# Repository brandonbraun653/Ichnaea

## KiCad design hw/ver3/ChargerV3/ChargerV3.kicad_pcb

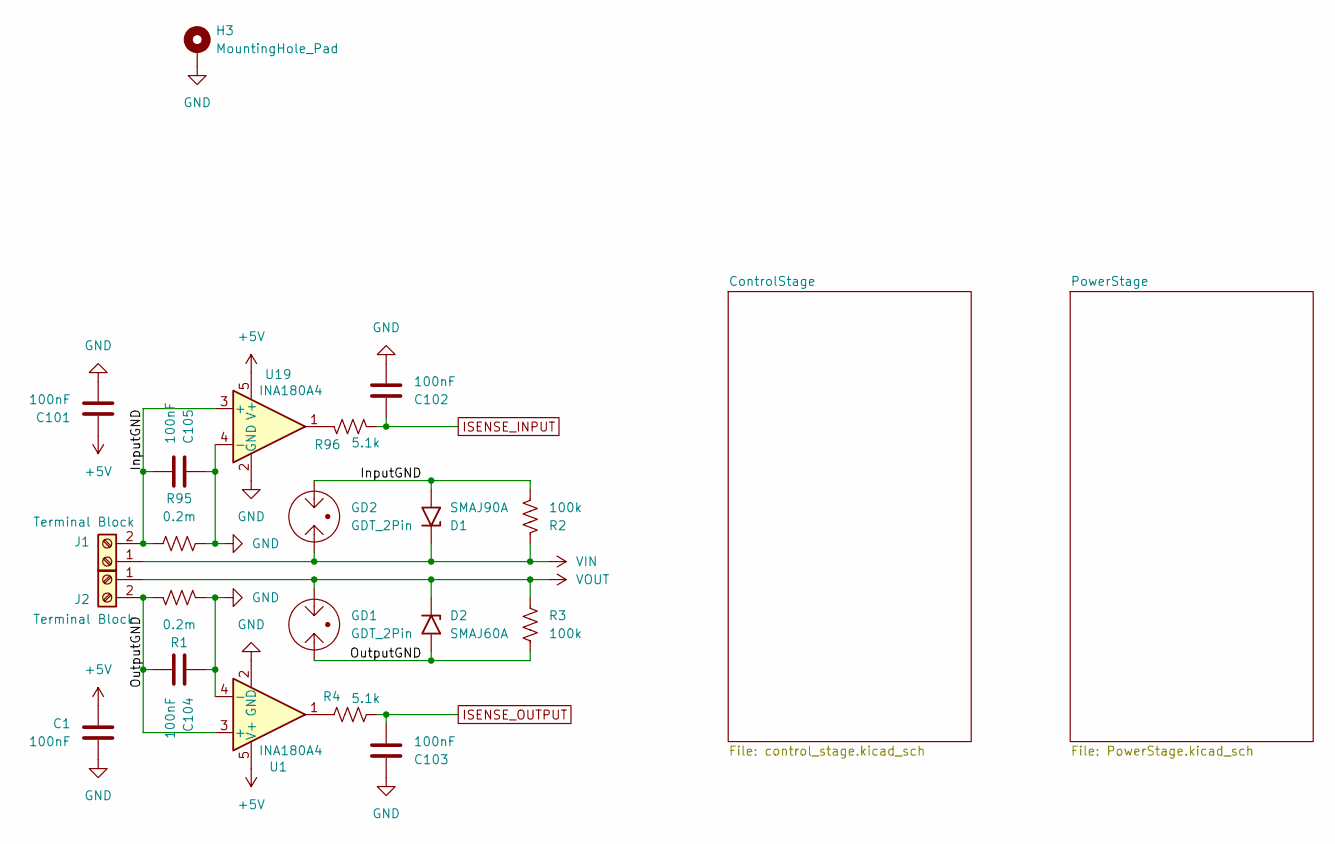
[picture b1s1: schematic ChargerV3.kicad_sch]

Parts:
C1, C101, C102, C103, C104, C105: 100nF; C_0603_1608Metric; LCSC C14663
D1: SMAJ90A; D_SMA; LCSC C2989723
D2: SMAJ60A; D_SMA; LCSC C707480
GD1, GD2: GDT_2Pin; Fuse_1812_4532Metric_Pad1.30x3.40mm_HandSolder; LCSC C78323
H3: MountingHole_Pad; MountingHole_3.2mm_M3_Pad_Via; Digikey N/A
J1, J2: Terminal Block; KF88SA-16.0-2P; LCSC C707749
R1, R95: 0.2m; Shunt_5930; LCSC C22446543
R2, R3: 100k; R_1206_3216Metric; LCSC C17900
R4, R96: 5.1k; R_0603_1608Metric; LCSC C23186
U1, U19: INA180A4; SOT-23-5; LCSC C188337

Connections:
+5V: C1.1, C101.1, U1.5 (V+), U19.5 (V+); also elsewhere on the board
/InputGND: C105.2, D1.2 (A2), GD2.2, J1.2, R2.2, R95.1, U19.3 (+)
/OutputGND: C104.2, D2.2 (A2), GD1.1, J2.2, R1.1, R3.2, U1.3 (+)
GND: C1.2, C101.2, C102.2, C103.1, C104.1, C105.1, H3.1, R1.2, R95.2, U1.2 (GND), U1.4 (-), U19.2 (GND), U19.4 (-); also elsewhere on the board
ISENSE_INPUT: C102.1, R96.1; also elsewhere on the board
ISENSE_OUTPUT: C103.2, R4.1; also elsewhere on the board
unnamed: R4.2, U1.1
unnamed: R96.2, U19.1
VIN: D1.1 (A1), GD2.1, J1.1, R2.1; also elsewhere on the board
VOUT: D2.1 (A1), GD1.2, J2.1, R3.1; also elsewhere on the board

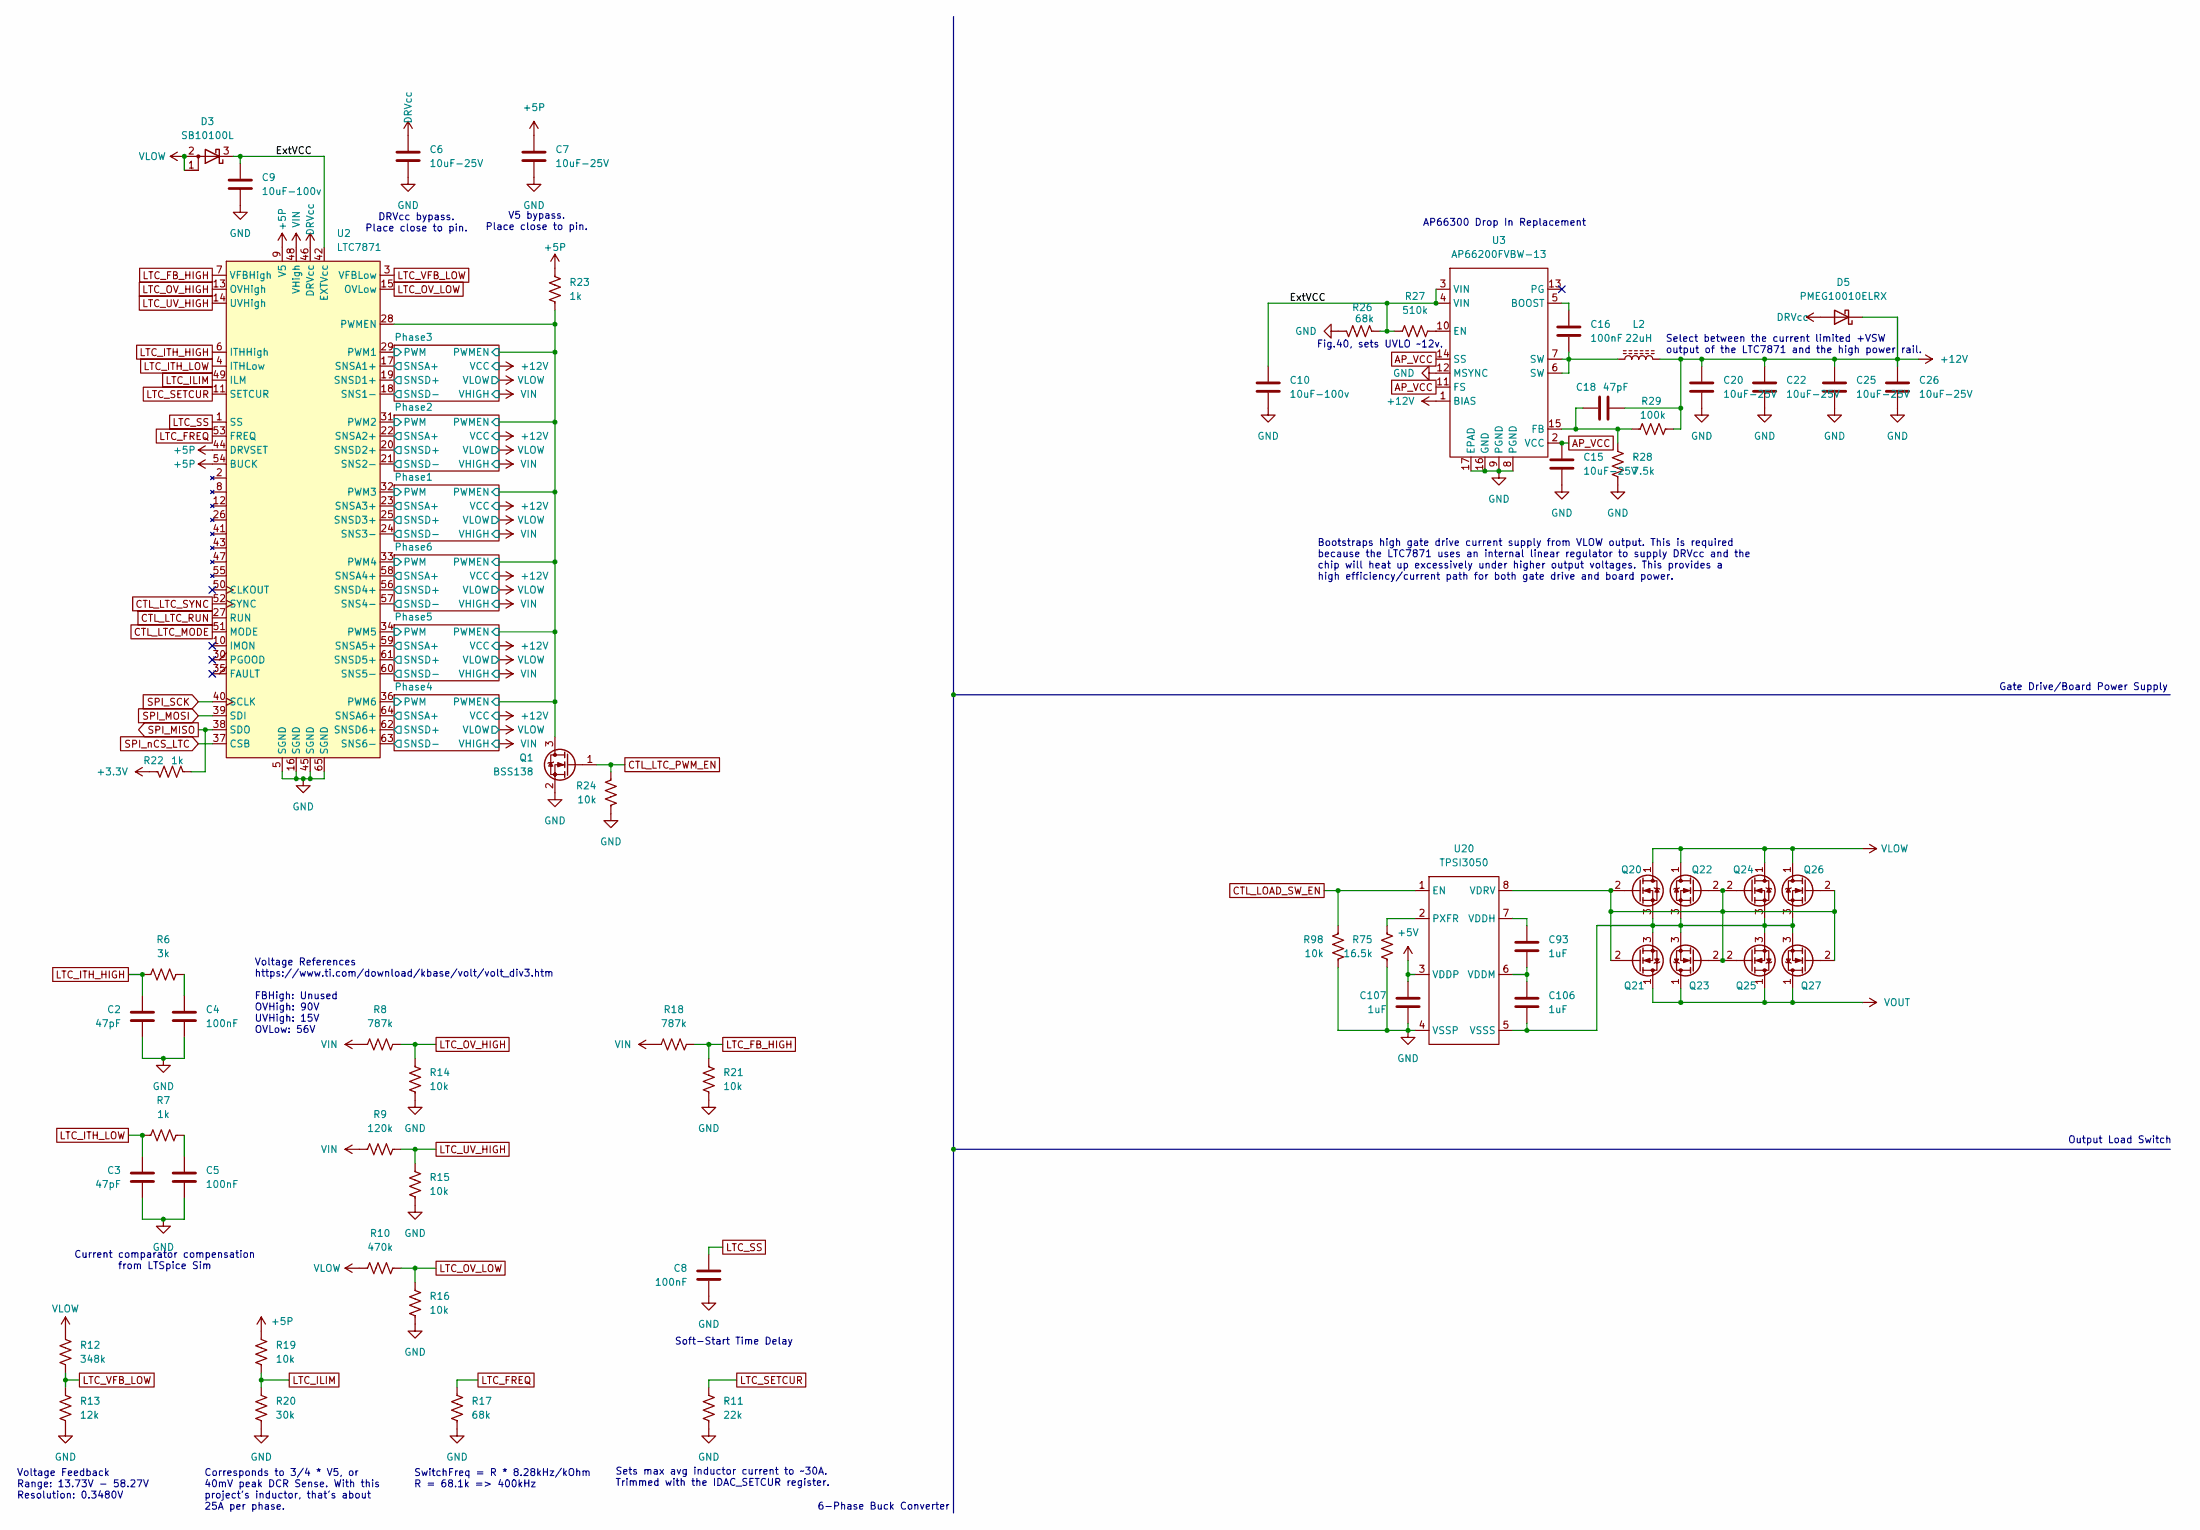
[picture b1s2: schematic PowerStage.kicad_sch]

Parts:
C2, C3, C18: 47pF; C_0603_1608Metric; LCSC C1671
C4, C5, C8, C16: 100nF; C_0603_1608Metric; LCSC C14663
C6: 10uF-25V; C_0603_1608Metric; Voltage 25; Digikey N/A
C7, C15, C20, C22, C25, C26: 10uF-25V; C_0603_1608Metric; Digikey N/A
C9, C10: 10uF-100v; C_1210_3225Metric_Pad1.33x2.70mm_HandSolder; Digikey 445-CGA6P1X7R1N106M250ACCT-ND
C93, C106, C107: 1uF; C_0603_1608Metric; LCSC C15849
D3: SB10100L; TO-277A; LCSC C113946
D5: PMEG10010ELRX; D_SOD-123; LCSC C179426
L2: 22uH; L_Wuerth_HCI-1040; Digikey N/A
Q1: BSS138; SOT-23; Digikey 5272-BSS138CT-ND
Q20, Q21, Q22, Q23, Q24, Q25, Q26, Q27: HYG053N10NS1C2; TRANS_BSC076N06NS3-G; Digikey N/A
R6: 3k; R_0603_1608Metric; Digikey N/A
R7, R22: 1k; R_0603_1608Metric; Digikey N/A
R8, R18: 787k; R_0805_2012Metric; Digikey P787KHCT-ND
R9: 120k; R_0805_2012Metric; Digikey N/A
R10: 470k; R_0805_2012Metric; LCSC C17709
R11: 22k; R_0603_1608Metric; LCSC C31850
R12: 348k; R_0603_1608Metric; LCSC C23006
R13: 12k; R_0603_1608Metric; LCSC C22790
R14, R15, R16, R19, R21, R24, R98: 10k; R_0603_1608Metric; LCSC C25804
R17: 68k; R_0603_1608Metric; Digikey N/A
R20: 30k; R_0603_1608Metric; Digikey N/A
R23: 1k; R_0603_1608Metric; LCSC C21190
R26: 68k; R_0603_1608Metric; LCSC C23231
R27: 510k; R_0603_1608Metric; LCSC C23192
R28: 7.5k; R_0603_1608Metric; LCSC C23234
R29: 100k; R_0603_1608Metric; LCSC C25803
R75: 16.5k; R_0603_1608Metric; LCSC C2933155
U2: LTC7871; LQFP-64-1EP_10x10mm_P0.5mm_EP6.5x6.5mm; Digikey 505-LTC7871ELWE#PBF-ND
U3: AP66200FVBW-13; QFN-16-1EP_4x4mm_P0.65mm_EP2.5x2.5mm; Digikey 31-AP66200FVBW-13CT-ND
U20: TPSI3050; SOIC-8_7.5x5.85mm_P1.27mm

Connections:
+3.3V: R22.2; also elsewhere on the board
+5P: C7.1, R19.2, R23.2, U2.9 (V5), U2.44 (DRVSET), U2.54 (BUCK)
+5V: C107.1, U20.3 (VDDP); also elsewhere on the board
+12V: C18.2, C20.1, C22.1, C25.1, C26.1, D5.1 (K), L2.2, R29.2, U3.1 (BIAS); also elsewhere on the board
/PowerStage/ExtVCC: C9.1, C10.1, D3.3 (K), R26.1, R27.1, U2.42 (EXTVcc), U3.3 (VIN), U3.4 (VIN)
/PowerStage/Phase1/PWM: U2.32 (PWM3); also elsewhere on the board
/PowerStage/Phase1/PWMEN: Q1.3 (D), R23.1, U2.28 (PWMEN); also elsewhere on the board
/PowerStage/Phase1/SNSA+: U2.23 (SNSA3+); also elsewhere on the board
/PowerStage/Phase1/SNSD+: U2.25 (SNSD3+); also elsewhere on the board
/PowerStage/Phase2/PWM: U2.31 (PWM2); also elsewhere on the board
/PowerStage/Phase2/SNSA+: U2.22 (SNSA2+); also elsewhere on the board
/PowerStage/Phase2/SNSD+: U2.20 (SNSD2+); also elsewhere on the board
/PowerStage/Phase3/PWM: U2.29 (PWM1); also elsewhere on the board
/PowerStage/Phase3/SNSA+: U2.17 (SNSA1+); also elsewhere on the board
/PowerStage/Phase3/SNSD+: U2.19 (SNSD1+); also elsewhere on the board
/PowerStage/Phase4/PWM: U2.36 (PWM6); also elsewhere on the board
/PowerStage/Phase4/SNSA+: U2.64 (SNSA6+); also elsewhere on the board
/PowerStage/Phase4/SNSD+: U2.62 (SNSD6+); also elsewhere on the board
/PowerStage/Phase5/PWM: U2.34 (PWM5); also elsewhere on the board
/PowerStage/Phase5/SNSA+: U2.59 (SNSA5+); also elsewhere on the board
/PowerStage/Phase5/SNSD+: U2.61 (SNSD5+); also elsewhere on the board
/PowerStage/Phase6/PWM: U2.33 (PWM4); also elsewhere on the board
/PowerStage/Phase6/SNSA+: U2.58 (SNSA4+); also elsewhere on the board
/PowerStage/Phase6/SNSD+: U2.56 (SNSD4+); also elsewhere on the board
AP_VCC: C15.1, U3.2 (VCC), U3.11 (FS), U3.14 (SS)
CTL_LOAD_SW_EN: R98.2, U20.1 (EN); also elsewhere on the board
CTL_LTC_MODE: U2.51 (MODE); also elsewhere on the board
CTL_LTC_PWM_EN: Q1.1 (G), R24.2; also elsewhere on the board
CTL_LTC_RUN: U2.27 (RUN); also elsewhere on the board
CTL_LTC_SYNC: U2.52 (SYNC); also elsewhere on the board
DRVcc: C6.1, D5.2 (A), U2.46 (DRVcc)
GND: C2.2, C3.2, C4.2, C5.2, C6.2, C7.2, C8.2, C9.2, C10.2, C15.2, C20.2, C22.2, C25.2, C26.2, C107.2, Q1.2 (S), R11.1, R13.1, R14.1, R15.1, R16.1, R17.1, R20.1, R21.1, R24.1, R26.2, R28.2, R75.2, R98.1, U2.5 (SGND), U2.16 (SGND), U2.45 (SGND), U2.65 (SGND), U3.8 (PGND), U3.9 (PGND), U3.12 (MSYNC), U3.16 (GND), U3.17 (EPAD), U20.4 (VSSP); also elsewhere on the board
LTC_FB_HIGH: R18.2, R21.2, U2.7 (VFBHigh)
LTC_FREQ: R17.2, U2.53 (FREQ)
LTC_ILIM: R19.1, R20.2, U2.49 (ILM)
LTC_ITH_HIGH: C2.1, R6.2, U2.6 (ITHHigh)
LTC_ITH_LOW: C3.1, R7.2, U2.4 (ITHLow)
LTC_OV_HIGH: R8.2, R14.2, U2.13 (OVHigh)
LTC_OV_LOW: R10.2, R16.2, U2.15 (OVLow)
LTC_SETCUR: R11.2, U2.11 (SETCUR)
LTC_SS: C8.1, U2.1 (SS)
LTC_UV_HIGH: R9.2, R15.2, U2.14 (UVHigh)
LTC_VFB_LOW: R12.1, R13.2, U2.3 (VFBLow)
unnamed: C4.1, R6.1
unnamed: C5.1, R7.1
unnamed: C16.2, L2.1, U3.6 (SW), U3.7 (SW)
unnamed: Q20.2 (G), Q21.2 (G), Q22.2 (G), Q23.2 (G), Q24.2 (G), Q25.2 (G), Q26.2 (G), Q27.2 (G), U20.8 (VDRV)
unnamed: C106.2, Q20.3 (S), Q21.3 (S), Q22.3 (S), Q23.3 (S), Q24.3 (S), Q25.3 (S), Q26.3 (S), Q27.3 (S), U20.5 (VSSS)
unnamed: C16.1, U3.5 (BOOST)
unnamed: R27.2, U3.10 (EN)
unnamed: C18.1, R28.1, R29.1, U3.15 (FB)
unnamed: R75.1, U20.2 (PXFR)
unnamed: C93.1, U20.7 (VDDH)
unnamed: C93.2, C106.1, U20.6 (VDDM)
SPI_MISO: R22.1, U2.38 (SDO); also elsewhere on the board
SPI_MOSI: U2.39 (SDI); also elsewhere on the board
SPI_SCK: U2.40 (SCLK); also elsewhere on the board
SPI_nCS_LTC: U2.37 (CSB); also elsewhere on the board
VIN: R8.1, R9.1, R18.1, U2.48 (VHigh); also elsewhere on the board
VLOW: D3.1 (A), D3.2 (A), Q20.1 (D), Q22.1 (D), Q24.1 (D), Q26.1 (D), R10.1, R12.2, U2.18 (SNS1-), U2.21 (SNS2-), U2.24 (SNS3-), U2.57 (SNS4-), U2.60 (SNS5-), U2.63 (SNS6-); also elsewhere on the board
VOUT: Q21.1 (D), Q23.1 (D), Q25.1 (D), Q27.1 (D); also elsewhere on the board

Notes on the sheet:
SwitchFreq = R * 8.28kHz/kOhm R = 68.1k => 400kHz
Output Load Switch
Fig.40, sets UVLO ~12v.
V5 bypass. Place close to pin.
Bootstraps high gate drive current supply from VLOW output. This is required because the LTC7871 uses an internal linear regulator to supply DRVcc and the chip will heat up excessively under higher output voltages. This provides a high efficiency/current path for both gate drive and board power.
Sets max avg inductor current to ~30A. Trimmed with the IDAC_SETCUR register.
Corresponds to 3/4 * V5, or 40mV peak DCR Sense. With this project's inductor, that's about 25A per phase.
6-Phase Buck Converter
Select between the current limited +VSW output of the LTC7871 and the high power rail.
Voltage Feedback Range: 13.73V - 58.27V Resolution: 0.3480V
Current comparator compensation from LTSpice Sim
Soft-Start Time Delay
AP66300 Drop In Replacement
Voltage References https://www.ti.com/download/kbase/volt/volt_div3.htm FBHigh: Unused OVHigh: 90V UVHigh: 15V OVLow: 56V
DRVcc bypass. Place close to pin.
Gate Drive/Board Power Supply

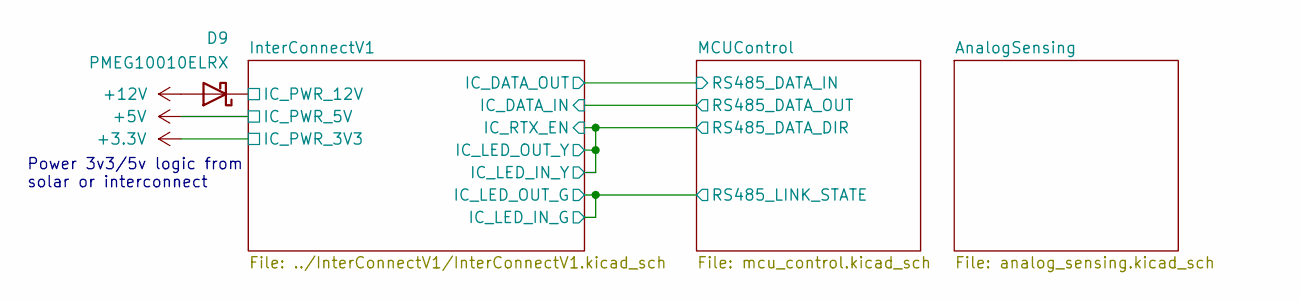
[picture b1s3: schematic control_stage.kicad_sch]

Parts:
D9: PMEG10010ELRX; D_SOD-123; LCSC C179426

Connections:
+12V: D9.2 (A); also elsewhere on the board
/ControlStage/InterConnectV1/IC_PWR_12V: D9.1 (K); also elsewhere on the board

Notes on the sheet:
Power 3v3/5v logic from solar or interconnect

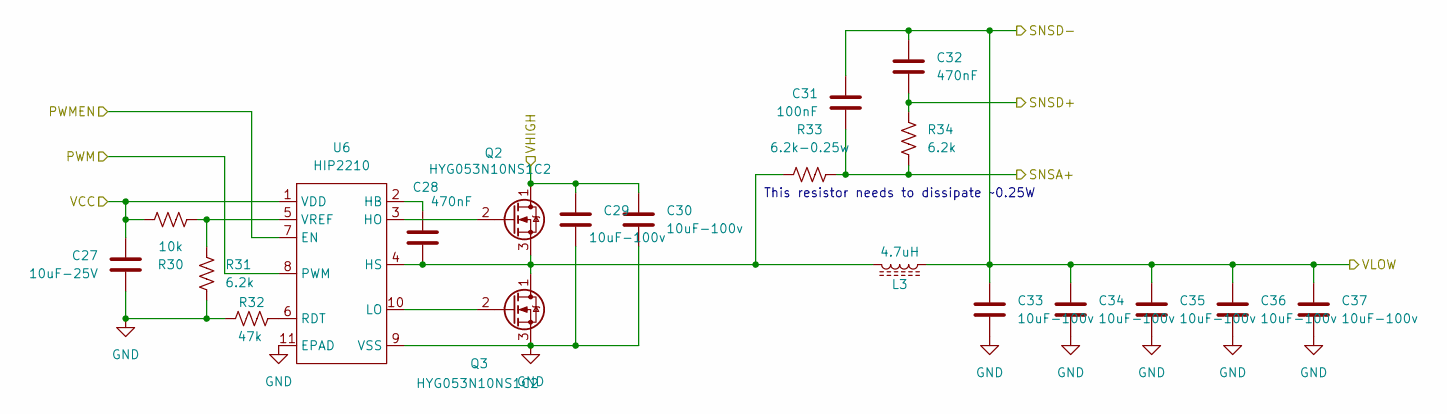
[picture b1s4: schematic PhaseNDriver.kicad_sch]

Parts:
C27: 10uF-25V; C_0603_1608Metric; Digikey N/A
C28, C32: 470nF; C_0603_1608Metric; Digikey N/A
C29, C30, C33, C34, C35, C36, C37: 10uF-100v; C_1210_3225Metric_Pad1.33x2.70mm_HandSolder; Digikey 445-CGA6P1X7R1N106M250ACCT-ND
C31: 100nF; C_0603_1608Metric; LCSC C14663
L3: 4.7uH; Bournes_L_PQ2614BLA; Digikey PQ2614BLA-3R3K-ND
Q2, Q3: HYG053N10NS1C2; TRANS_BSC076N06NS3-G; Digikey N/A
R30: 10k; R_0603_1608Metric; LCSC C25804
R31, R34: 6.2k; R_0603_1608Metric; Digikey N/A
R32: 47k; R_0603_1608Metric; Digikey N/A
R33: 6.2k-0.25w; R_1206_3216Metric_Pad1.30x1.75mm_HandSolder; Digikey 311-6.20KFRCT-ND
U6: HIP2210; TDFN-10-1EP_4x4mm_P0.8mm_EP2.6x3mm; Digikey 20-HIP2210FRTZ-TCT-ND

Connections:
+12V: C27.1, R30.1, U6.1 (VDD); also elsewhere on the board
/PowerStage/Phase1/PWM: U6.8 (PWM); also elsewhere on the board
/PowerStage/Phase1/PWMEN: U6.7 (EN); also elsewhere on the board
/PowerStage/Phase1/SNSA+: C31.2, R33.2, R34.2; also elsewhere on the board
/PowerStage/Phase1/SNSD+: C32.2, R34.1; also elsewhere on the board
GND: C27.2, C29.2, C30.2, C33.2, C34.2, C35.2, C36.2, C37.2, Q3.3 (S), R31.2, R32.1, U6.9 (VSS), U6.11 (EPAD); also elsewhere on the board
unnamed: Q2.2 (G), U6.3 (HO)
unnamed: C28.2, L3.2, Q2.3 (S), Q3.1 (D), R33.1, U6.4 (HS)
unnamed: Q3.2 (G), U6.10 (LO)
unnamed: C28.1, U6.2 (HB)
unnamed: R32.2, U6.6 (RDT)
unnamed: R30.2, R31.1, U6.5 (VREF)
VIN: C29.1, C30.1, Q2.1 (D); also elsewhere on the board
VLOW: C31.1, C32.1, C33.1, C34.1, C35.1, C36.1, C37.1, L3.1; also elsewhere on the board

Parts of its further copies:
C38, C49, C60, C71, C82: 10uF-25V; C_0603_1608Metric; Digikey N/A
C39, C43, C50, C54, C61, C65, C72, C76, C83, C87: 470nF; C_0603_1608Metric; Digikey N/A
C40, C41, C44, C45, C46, C47, C48, C51, C52, C55, C56, C57, C58, C59, C62, C63, C66, C67, C68, C69, C70, C73, C74, C77, C78, C79, C80, C81, C84, C85, C88, C89, C90, C91, C92: 10uF-100v; C_1210_3225Metric_Pad1.33x2.70mm_HandSolder; Digikey 445-CGA6P1X7R1N106M250ACCT-ND
C42, C53, C64, C75, C86: 100nF; C_0603_1608Metric; LCSC C14663
L4, L5, L6, L7, L8: 4.7uH; Bournes_L_PQ2614BLA; Digikey PQ2614BLA-3R3K-ND
Q4, Q5, Q6, Q7, Q8, Q9, Q10, Q11, Q17, Q18: HYG053N10NS1C2; TRANS_BSC076N06NS3-G; Digikey N/A
R35, R40, R45, R50, R69: 10k; R_0603_1608Metric; LCSC C25804
R36, R39, R41, R44, R46, R49, R51, R54, R70, R73: 6.2k; R_0603_1608Metric; Digikey N/A
R37, R42, R47, R52, R71: 47k; R_0603_1608Metric; Digikey N/A
R38, R43, R48, R53, R72: 6.2k-0.25w; R_1206_3216Metric_Pad1.30x1.75mm_HandSolder; Digikey 311-6.20KFRCT-ND
U7, U8, U9, U10, U11: HIP2210; TDFN-10-1EP_4x4mm_P0.8mm_EP2.6x3mm; Digikey 20-HIP2210FRTZ-TCT-ND

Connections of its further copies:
+12V: C38.1, C49.1, C60.1, C71.1, C82.1, R35.1, R40.1, R45.1, R50.1, R69.1, U7.1 (VDD), U8.1 (VDD), U9.1 (VDD), U10.1 (VDD), U11.1 (VDD); also elsewhere on the board
/PowerStage/Phase1/PWMEN: U7.7 (EN), U8.7 (EN), U9.7 (EN), U10.7 (EN), U11.7 (EN); also elsewhere on the board
/PowerStage/Phase2/PWM: U7.8 (PWM); also elsewhere on the board
/PowerStage/Phase2/SNSA+: C42.2, R38.2, R39.2; also elsewhere on the board
/PowerStage/Phase2/SNSD+: C43.2, R39.1; also elsewhere on the board
/PowerStage/Phase3/PWM: U8.8 (PWM); also elsewhere on the board
/PowerStage/Phase3/SNSA+: C53.2, R43.2, R44.2; also elsewhere on the board
/PowerStage/Phase3/SNSD+: C54.2, R44.1; also elsewhere on the board
/PowerStage/Phase4/PWM: U9.8 (PWM); also elsewhere on the board
/PowerStage/Phase4/SNSA+: C64.2, R48.2, R49.2; also elsewhere on the board
/PowerStage/Phase4/SNSD+: C65.2, R49.1; also elsewhere on the board
/PowerStage/Phase5/PWM: U10.8 (PWM); also elsewhere on the board
/PowerStage/Phase5/SNSA+: C75.2, R53.2, R54.2; also elsewhere on the board
/PowerStage/Phase5/SNSD+: C76.2, R54.1; also elsewhere on the board
/PowerStage/Phase6/PWM: U11.8 (PWM); also elsewhere on the board
/PowerStage/Phase6/SNSA+: C86.2, R72.2, R73.2; also elsewhere on the board
/PowerStage/Phase6/SNSD+: C87.2, R73.1; also elsewhere on the board
GND: C38.2, C40.2, C41.2, C44.2, C45.2, C46.2, C47.2, C48.2, C49.2, C51.2, C52.2, C55.2, C56.2, C57.2, C58.2, C59.2, C60.2, C62.2, C63.2, C66.2, C67.2, C68.2, C69.2, C70.2, C71.2, C73.2, C74.2, C77.2, C78.2, C79.2, C80.2, C81.2, C82.2, C84.2, C85.2, C88.2, C89.2, C90.2, C91.2, C92.2, Q5.3 (S), Q7.3 (S), Q9.3 (S), Q11.3 (S), Q18.3 (S), R36.2, R37.1, R41.2, R42.1, R46.2, R47.1, R51.2, R52.1, R70.2, R71.1, U7.9 (VSS), U7.11 (EPAD), U8.9 (VSS), U8.11 (EPAD), U9.9 (VSS), U9.11 (EPAD), U10.9 (VSS), U10.11 (EPAD), U11.9 (VSS), U11.11 (EPAD); also elsewhere on the board
unnamed: Q4.2 (G), U7.3 (HO)
unnamed: C39.2, L4.2, Q4.3 (S), Q5.1 (D), R38.1, U7.4 (HS)
unnamed: Q5.2 (G), U7.10 (LO)
unnamed: Q6.2 (G), U8.3 (HO)
unnamed: C50.2, L5.2, Q6.3 (S), Q7.1 (D), R43.1, U8.4 (HS)
unnamed: Q7.2 (G), U8.10 (LO)
unnamed: Q8.2 (G), U9.3 (HO)
unnamed: C61.2, L6.2, Q8.3 (S), Q9.1 (D), R48.1, U9.4 (HS)
unnamed: Q9.2 (G), U9.10 (LO)
unnamed: Q10.2 (G), U10.3 (HO)
unnamed: C72.2, L7.2, Q10.3 (S), Q11.1 (D), R53.1, U10.4 (HS)
unnamed: Q11.2 (G), U10.10 (LO)
unnamed: Q17.2 (G), U11.3 (HO)
unnamed: C83.2, L8.2, Q17.3 (S), Q18.1 (D), R72.1, U11.4 (HS)
unnamed: Q18.2 (G), U11.10 (LO)
unnamed: C39.1, U7.2 (HB)
unnamed: R37.2, U7.6 (RDT)
unnamed: R35.2, R36.1, U7.5 (VREF)
unnamed: C50.1, U8.2 (HB)
unnamed: R42.2, U8.6 (RDT)
unnamed: R40.2, R41.1, U8.5 (VREF)
unnamed: C61.1, U9.2 (HB)
unnamed: R47.2, U9.6 (RDT)
unnamed: R45.2, R46.1, U9.5 (VREF)
unnamed: C72.1, U10.2 (HB)
unnamed: R52.2, U10.6 (RDT)
unnamed: R50.2, R51.1, U10.5 (VREF)
unnamed: C83.1, U11.2 (HB)
unnamed: R71.2, U11.6 (RDT)
unnamed: R69.2, R70.1, U11.5 (VREF)
VIN: C40.1, C41.1, C51.1, C52.1, C62.1, C63.1, C73.1, C74.1, C84.1, C85.1, Q4.1 (D), Q6.1 (D), Q8.1 (D), Q10.1 (D), Q17.1 (D); also elsewhere on the board
VLOW: C42.1, C43.1, C44.1, C45.1, C46.1, C47.1, C48.1, C53.1, C54.1, C55.1, C56.1, C57.1, C58.1, C59.1, C64.1, C65.1, C66.1, C67.1, C68.1, C69.1, C70.1, C75.1, C76.1, C77.1, C78.1, C79.1, C80.1, C81.1, C86.1, C87.1, C88.1, C89.1, C90.1, C91.1, C92.1, L4.1, L5.1, L6.1, L7.1, L8.1; also elsewhere on the board

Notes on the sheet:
This resistor needs to dissipate ~0.25W

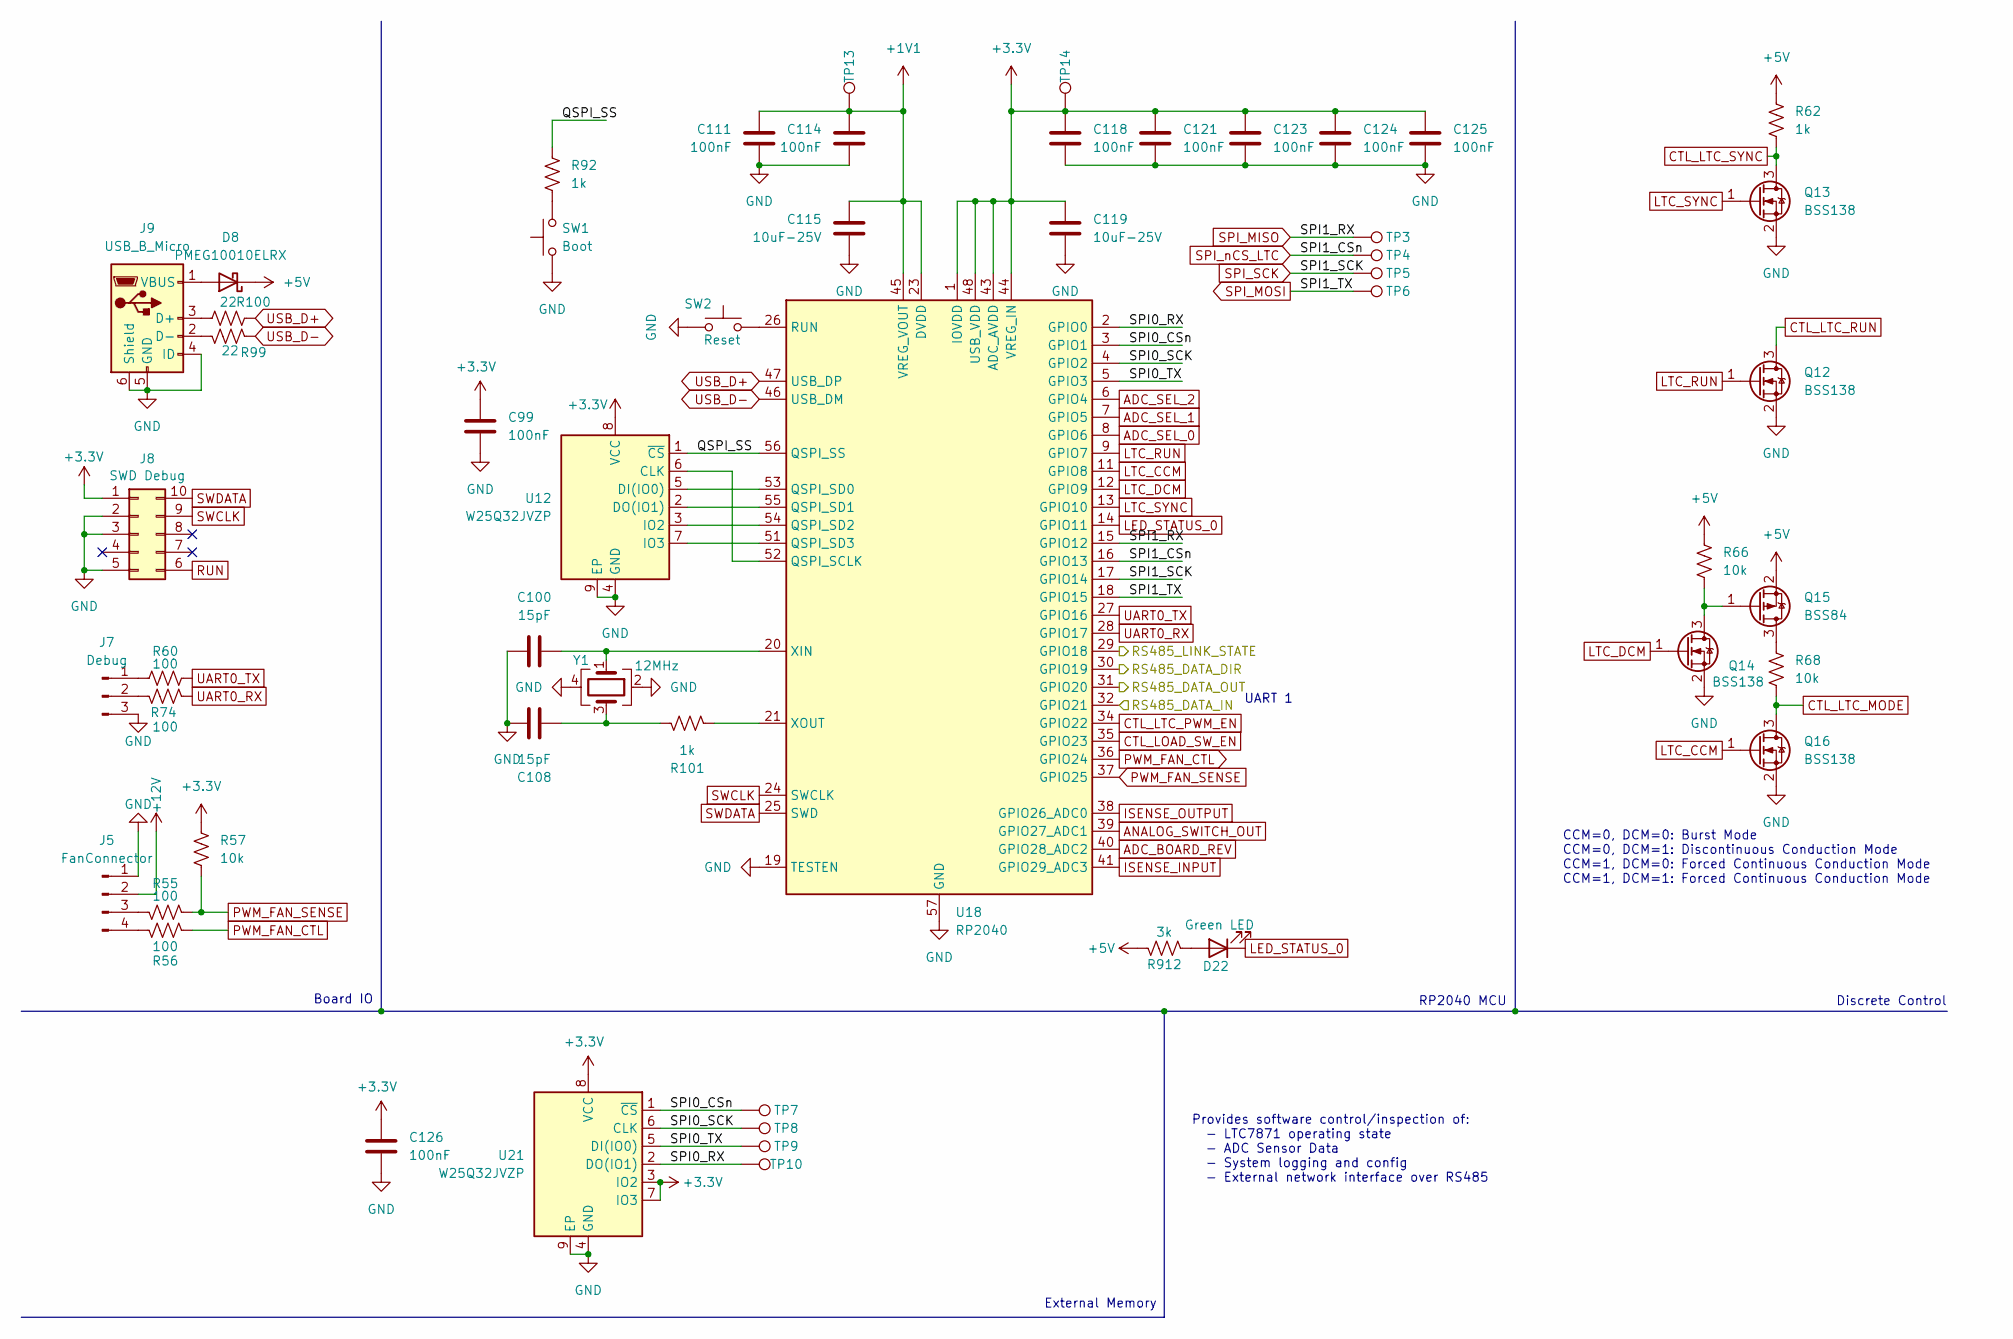
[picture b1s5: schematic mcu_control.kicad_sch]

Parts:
C99, C111, C114, C118, C121, C123, C124, C125, C126: 100nF; C_0603_1608Metric; LCSC C14663
C100, C108: 15pF; C_0603_1608Metric; Digikey N/A
C115, C119: 10uF-25V; C_0603_1608Metric; Digikey N/A
D8: PMEG10010ELRX; D_SOD-123; LCSC C179426
D22: Green LED; LED_0805_2012Metric; LCSC C2297
J5: FanConnector; Molex_KK-254_AE-6410-04A_1x04_P2.54mm_Vertical; Digikey WM4330-ND
J7: Debug; PinHeader_1x03_P2.54mm_Vertical; Digikey N/A
J8: SWD Debug; JTAG_2x05_P1_27mm_Shrouded_SMD; Digikey 1175-1629-ND
J9: USB_B_Micro; Amphenol-MicroB; LCSC C132350
Q12, Q13, Q14, Q16: BSS138; SOT-23; Digikey 5272-BSS138CT-ND
Q15: BSS84; SOT-23; Digikey 5272-BSS84CT-ND
R55, R56, R60, R74: 100; R_0603_1608Metric; Digikey N/A
R57, R66, R68: 10k; R_0603_1608Metric; LCSC C25804
R62, R92: 1k; R_0603_1608Metric; LCSC C21190
R99, R100: 22; R_0603_1608Metric; LCSC C23345
R101: 1k; R_0603_1608Metric; Digikey N/A
R912: 3k; R_0603_1608Metric; LCSC C126358
SW1: Boot; SW_Tactile_SPST_NO_Straight_CK_PTS636Sx25SMTRLFS; Digikey CKN12321-2-ND
SW2: Reset; SW_Tactile_SPST_NO_Straight_CK_PTS636Sx25SMTRLFS; Digikey CKN12321-2-ND
TP3, TP4, TP5, TP6, TP7, TP8, TP9, TP10, TP13, TP14: TestPoint; TestPoint_Pad_D1.0mm; LCSC N/A
U12, U21: W25Q32JVZP; WSON-8-1EP_6x5mm_P1.27mm_EP3.4x4.3mm; Digikey W25Q32JVZPIQ-ND
U18: RP2040; QFN-56-1EP_7x7mm_P0.4mm_EP3.2x3.2mm; Digikey 2648-SC0914(13)CT-ND
Y1: 12MHz; Crystal_SMD_3225-4Pin_3.2x2.5mm; Digikey XC2613CT-ND

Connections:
+1V1: C111.1, C114.1, C115.1, TP13.1, U18.23 (DVDD), U18.45 (VREG_VOUT), U18.50 (DVDD)
+3.3V: C99.1, C118.1, C119.1, C121.1, C123.1, C124.1, C125.1, C126.1, J8.1, R57.2, TP14.1, U12.8 (VCC), U18.1 (IOVDD), U18.10 (IOVDD), U18.22 (IOVDD), U18.33 (IOVDD), U18.42 (IOVDD), U18.43 (ADC_AVDD), U18.44 (VREG_IN), U18.48 (USB_VDD), U18.49 (IOVDD), U21.3 (IO2), U21.7 (IO3), U21.8 (VCC); also elsewhere on the board
+5V: D8.1 (K), Q15.2 (S), R62.2, R66.2, R912.2; also elsewhere on the board
+12V: J5.2; also elsewhere on the board
/ControlStage/InterConnectV1/IC_DATA_IN: U18.31 (GPIO20); also elsewhere on the board
/ControlStage/InterConnectV1/IC_DATA_OUT: U18.32 (GPIO21); also elsewhere on the board
/ControlStage/InterConnectV1/IC_LED_IN_G: U18.29 (GPIO18); also elsewhere on the board
/ControlStage/InterConnectV1/IC_LED_IN_Y: U18.30 (GPIO19); also elsewhere on the board
/ControlStage/MCUControl/QSPI_SS: R92.2, U12.1 (~CS), U18.56 (QSPI_SS)
/ControlStage/MCUControl/SPI0_CSn: TP7.1, U18.3 (GPIO1), U21.1 (~CS)
/ControlStage/MCUControl/SPI0_RX: TP10.1, U18.2 (GPIO0), U21.2 (DO(IO1))
/ControlStage/MCUControl/SPI0_SCK: TP8.1, U18.4 (GPIO2), U21.6 (CLK)
/ControlStage/MCUControl/SPI0_TX: TP9.1, U18.5 (GPIO3), U21.5 (DI(IO0))
ADC_BOARD_REV: U18.40 (GPIO28_ADC2); also elsewhere on the board
ADC_SEL_0: U18.8 (GPIO6); also elsewhere on the board
ADC_SEL_1: U18.7 (GPIO5); also elsewhere on the board
ADC_SEL_2: U18.6 (GPIO4); also elsewhere on the board
ANALOG_SWITCH_OUT: U18.39 (GPIO27_ADC1); also elsewhere on the board
CTL_LOAD_SW_EN: U18.35 (GPIO23); also elsewhere on the board
CTL_LTC_MODE: Q16.3 (D), R68.2; also elsewhere on the board
CTL_LTC_PWM_EN: U18.34 (GPIO22); also elsewhere on the board
CTL_LTC_RUN: Q12.3 (D); also elsewhere on the board
CTL_LTC_SYNC: Q13.3 (D), R62.1; also elsewhere on the board
GND: C99.2, C100.1, C108.1, C111.2, C114.2, C115.2, C118.2, C119.2, C121.2, C123.2, C124.2, C125.2, C126.2, J5.1, J7.3, J8.2, J8.3, J8.5, J9.4 (ID), J9.5 (GND), J9.6 (Shield), Q12.2 (S), Q13.2 (S), Q14.2 (S), Q16.2 (S), SW1.1, SW2.1, U12.4 (GND), U12.9 (EP), U18.19 (TESTEN), U18.57 (GND), U21.4 (GND), U21.9 (EP), Y1.2, Y1.4; also elsewhere on the board
ISENSE_INPUT: U18.41 (GPIO29_ADC3); also elsewhere on the board
ISENSE_OUTPUT: U18.38 (GPIO26_ADC0); also elsewhere on the board
LED_STATUS_0: D22.1 (K), U18.14 (GPIO11)
LTC_CCM: Q16.1 (G), U18.11 (GPIO8)
LTC_DCM: Q14.1 (G), U18.12 (GPIO9)
LTC_RUN: Q12.1 (G), U18.9 (GPIO7)
LTC_SYNC: Q13.1 (G), U18.13 (GPIO10)
unnamed: C108.2, R101.1, Y1.3
unnamed: D8.2 (A), J9.1 (VBUS)
unnamed: D22.2 (A), R912.1
unnamed: J5.3, R55.2
unnamed: J5.4, R56.1
unnamed: J7.1, R60.1
unnamed: J7.2, R74.1
unnamed: J9.3 (D+), R100.2
unnamed: J9.2 (D-), R99.2
unnamed: Q14.3 (D), Q15.1 (G), R66.1
unnamed: Q15.3 (D), R68.1
unnamed: R92.1, SW1.2
unnamed: U12.6 (CLK), U18.52 (QSPI_SCLK)
unnamed: U12.5 (DI(IO0)), U18.53 (QSPI_SD0)
unnamed: U12.2 (DO(IO1)), U18.55 (QSPI_SD1)
unnamed: U12.3 (IO2), U18.54 (QSPI_SD2)
unnamed: U12.7 (IO3), U18.51 (QSPI_SD3)
unnamed: SW2.2, U18.26 (RUN)
unnamed: C100.2, U18.20 (XIN), Y1.1
unnamed: R101.2, U18.21 (XOUT)
PWM_FAN_CTL: R56.2, U18.36 (GPIO24)
PWM_FAN_SENSE: R55.1, R57.1, U18.37 (GPIO25)
RUN: J8.6
SPI_MISO: TP3.1, U18.15 (GPIO12); also elsewhere on the board
SPI_MOSI: TP6.1, U18.18 (GPIO15); also elsewhere on the board
SPI_SCK: TP5.1, U18.17 (GPIO14); also elsewhere on the board
SPI_nCS_LTC: TP4.1, U18.16 (GPIO13); also elsewhere on the board
SWCLK: J8.9, U18.24 (SWCLK)
SWDATA: J8.10, U18.25 (SWD)
UART0_RX: R74.2, U18.28 (GPIO17)
UART0_TX: R60.2, U18.27 (GPIO16)
USB_D+: R100.1, U18.47 (USB_DP)
USB_D-: R99.1, U18.46 (USB_DM)

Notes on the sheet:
Board IO
UART 1
Provides software control/inspection of: - LTC7871 operating state - ADC Sensor Data - System logging and config - External network interface over RS485
Discrete Control
External Memory
CCM=0, DCM=0: Burst Mode CCM=0, DCM=1: Discontinuous Conduction Mode CCM=1, DCM=0: Forced Continuous Conduction Mode CCM=1, DCM=1: Forced Continuous Conduction Mode
RP2040 MCU

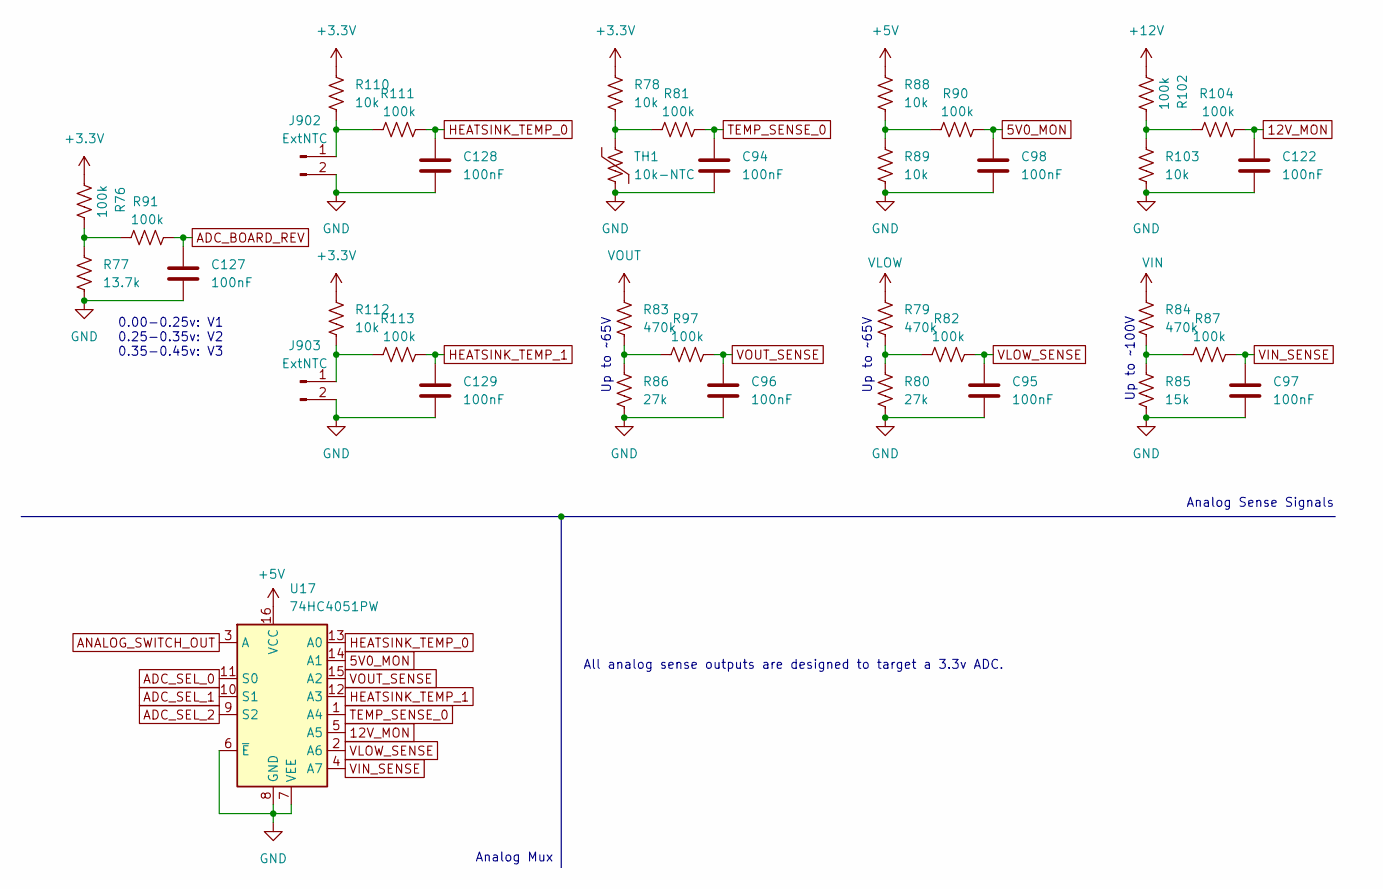
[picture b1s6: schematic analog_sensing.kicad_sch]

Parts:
C94, C95, C96, C97, C98, C122, C127, C128, C129: 100nF; C_0603_1608Metric; LCSC C14663
J902, J903: ExtNTC; PinHeader_1x02_P2.54mm_Vertical
R76, R81, R82, R87, R90, R91, R97, R102, R104, R111, R113: 100k; R_0603_1608Metric; LCSC C25803
R77: 13.7k; R_0603_1608Metric; LCSC C2930064
R78, R88, R89, R103, R110, R112: 10k; R_0603_1608Metric; LCSC C25804
R79, R83: 470k; R_0805_2012Metric; Digikey N/A
R80, R86: 27k; R_0603_1608Metric; Digikey N/A
R84: 470k; R_0805_2012Metric; LCSC C17709
R85: 15k; R_0603_1608Metric; Digikey N/A
TH1: 10k-NTC; R_0402_1005Metric_Pad0.72x0.64mm_HandSolder; Digikey 445-2550-1-ND
U17: 74HC4051PW; TSSOP-16_4.4x5mm_P0.65mm; Digikey 1727-3064-1-ND

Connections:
5V0_MON: C98.1, R90.2, U17.14 (A1)
12V_MON: C122.1, R104.2, U17.5 (A5)
+3.3V: R76.1, R78.2, R110.2, R112.2; also elsewhere on the board
+5V: R88.2, U17.16 (VCC); also elsewhere on the board
+12V: R102.1; also elsewhere on the board
ADC_BOARD_REV: C127.1, R91.2; also elsewhere on the board
ADC_SEL_0: U17.11 (S0); also elsewhere on the board
ADC_SEL_1: U17.10 (S1); also elsewhere on the board
ADC_SEL_2: U17.9 (S2); also elsewhere on the board
ANALOG_SWITCH_OUT: U17.3 (A); also elsewhere on the board
GND: C94.2, C95.2, C96.2, C97.2, C98.2, C122.2, C127.2, C128.2, C129.2, J902.2, J903.2, R77.1, R80.1, R85.1, R86.1, R89.1, R103.1, TH1.2, U17.6 (~E), U17.7 (VEE), U17.8 (GND); also elsewhere on the board
HEATSINK_TEMP_0: C128.1, R111.2, U17.13 (A0)
HEATSINK_TEMP_1: C129.1, R113.2, U17.12 (A3)
unnamed: J902.1, R110.1, R111.1
unnamed: J903.1, R112.1, R113.1
unnamed: R76.2, R77.2, R91.1
unnamed: R78.1, R81.1, TH1.1
unnamed: R79.1, R80.2, R82.1
unnamed: R83.1, R86.2, R97.1
unnamed: R84.1, R85.2, R87.1
unnamed: R88.1, R89.2, R90.1
unnamed: R102.2, R103.2, R104.1
TEMP_SENSE_0: C94.1, R81.2, U17.1 (A4)
VIN: R84.2; also elsewhere on the board
VIN_SENSE: C97.1, R87.2, U17.4 (A7)
VLOW: R79.2; also elsewhere on the board
VLOW_SENSE: C95.1, R82.2, U17.2 (A6)
VOUT: R83.2; also elsewhere on the board
VOUT_SENSE: C96.1, R97.2, U17.15 (A2)

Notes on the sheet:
Up to ~65V
Analog Sense Signals
0.00-0.25v: V1 0.25-0.35v: V2 0.35-0.45v: V3
Up to ~100V
Analog Mux
All analog sense outputs are designed to target a 3.3v ADC.
